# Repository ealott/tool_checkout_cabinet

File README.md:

# Wifi-Enabled RFID Cabinet Lock
An inexpensive, RFID-based door access solution for individual cabinets.  Based on Micropython and the ESP8266/ESP32 MCU.

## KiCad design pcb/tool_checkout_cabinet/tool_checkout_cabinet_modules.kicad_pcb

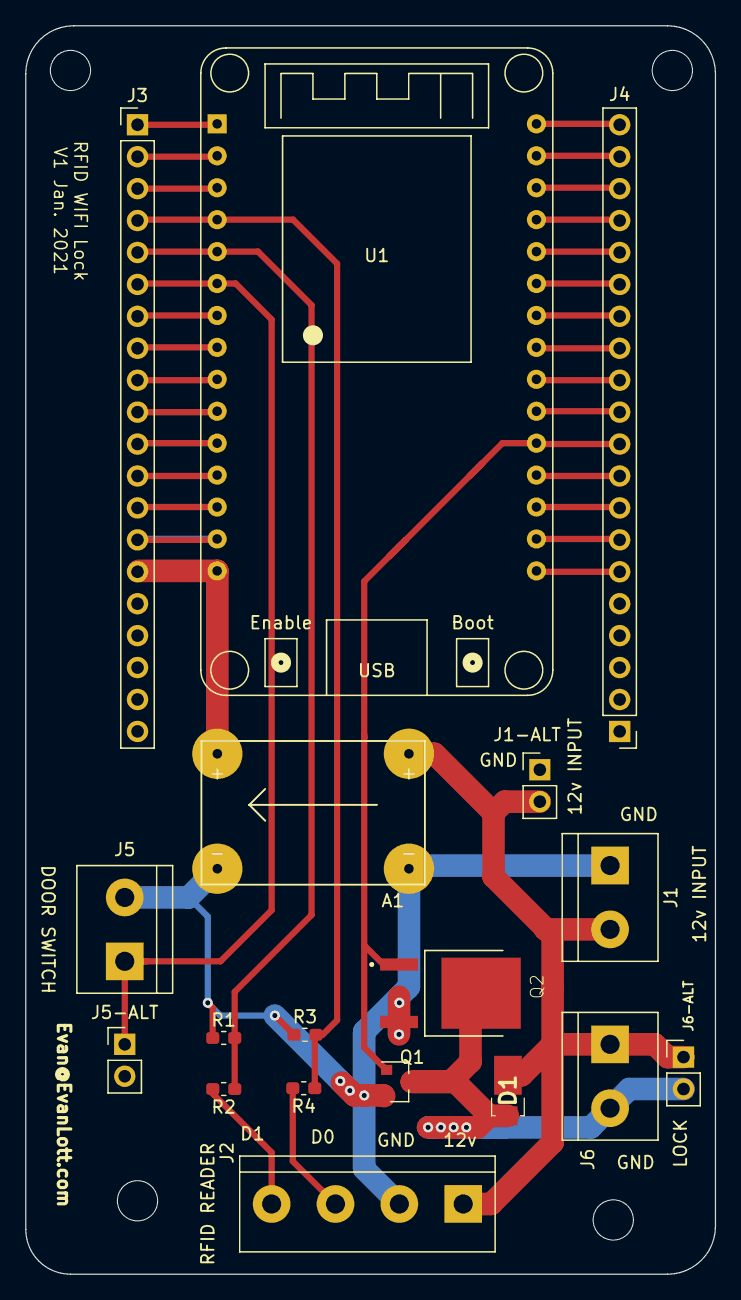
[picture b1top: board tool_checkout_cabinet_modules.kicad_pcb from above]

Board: 2 copper layers, 54.9 x 99.3 mm, 18 parts (0 on the bottom side), 33 nets.

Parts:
A1: Mini360_Module
D1: V8PAM10S-M3_H; V8PAM10SHM3H
J1, J5, J6: Screw_Terminal_01x02; TerminalBlock_bornier-2_P5.08mm
J1-ALT, J5-ALT, J6-ALT: PinHeader_1x02_P2.54mm_Vertical
J2: Screw_Terminal_01x04; TerminalBlock_bornier-4_P5.08mm
J3, J4: Conn_01x20_Male; PinHeader_1x20_P2.54mm_Vertical
Q1: DMG2302U; SOT-23
Q2: AOD4184A; DPAK228P994X240-4N
R1, R3: 10k; R_0603_1608Metric_Pad1.05x0.95mm_HandSolder
R2, R4: 4k7; R_0603_1608Metric_Pad1.05x0.95mm_HandSolder
U1: ESP32_DevKit_V1_DOIT; esp32_devkit_v1_doit

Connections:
+5V: A1.3, J3.15, U1.15
GND: A1.2, A1.4, J1.1, J1-ALT.1, J2.2, J3.14, J4.7, J5.2, J5-ALT.2, Q1.2, Q2.3, R1.1, R3.1, U1.14, U1.17
IO4: J4.10, Q1.1, Q2.1, U1.20
IO32: J3.6, J5.1, J5-ALT.1, U1.6
IO34: J3.4, R3.2, R4.1, U1.4
IO35: J3.5, R1.2, R2.1, U1.5
J6-12v: A1.1, D1.1, J1.2, J1-ALT.2, J2.1, J6.1, J6-ALT.1
unnamed: D1.2, J6.2, J6-ALT.2, Q1.3, Q2.4
unnamed: J2.3, R4.2
unnamed: J2.4, R2.2
unnamed: J3.1, U1.1
unnamed: J3.2, U1.2
unnamed: J3.3, U1.3
unnamed: J3.7, U1.7
unnamed: J3.8, U1.8
unnamed: J3.9, U1.9
unnamed: J3.10, U1.10
unnamed: J3.11, U1.11
unnamed: J3.12, U1.12
unnamed: J3.13, U1.13
unnamed: J4.6, U1.16
unnamed: J4.8, U1.18
unnamed: J4.9, U1.19
unnamed: J4.11, U1.21
unnamed: J4.12, U1.22
unnamed: J4.13, U1.23
unnamed: J4.14, U1.24
unnamed: J4.15, U1.25
unnamed: J4.16, U1.26
unnamed: J4.17, U1.27
unnamed: J4.18, U1.28
unnamed: J4.19, U1.29
unnamed: J4.20, U1.30

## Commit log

2020-08-30 initial commit of working system
2020-08-30 added bad read detection
2020-11-02 add some TODOs
2020-11-13 initial commit of PCB design
2020-11-13 renamed block diagram png
2020-11-13 Update README.md
    add esp32 to description
2021-01-28 v1 update
2021-01-28 Add 3D render image of PCB
2021-04-13 initial commit of AD caching system
2021-04-13 reorganize w/ docs directory; update KiCad project
2021-04-16 improve filename
2021-04-16 prune requirements
2021-04-16 initial commit of SystemD service file, makefile, env
2021-04-16 store some settings in ENV variables, add dotenv
2021-04-21 add dockerfile
2021-04-21 update entrypoint
2021-04-23 wait for network-online before starting service
2021-04-23 install python3-ldap package through system repos
2021-04-25 Fix broken image reference.
2021-05-31 Initital commit of working firmware
2021-07-30 Update to use caching, and properly convert raw RFID output to 10D format
2021-07-30 added output for 40bit IDs; removed unused arg; changed lock open time from 5 to 2 sec
2021-08-04 fixed bit mask
2022-03-21 Bump waitress from 2.0.0 to 2.1.1 in /ad_cache
    Bumps [waitress](https://github.com/Pylons/waitress) from 2.0.0 to 2.1.1.
    - [Release notes](https://github.com/Pylons/waitress/releases)
    - [Changelog](https://github.com/Pylons/waitress/blob/master/CHANGES.txt)
    - [Commits](https://github.com/Pylons/waitress/compare/v2.0.0...v2.1.1)
    ---
    updated-dependencies:
2023-02-16 Bump werkzeug from 1.0.1 to 2.2.3 in /ad_cache
    Bumps [werkzeug](https://github.com/pallets/werkzeug) from 1.0.1 to 2.2.3.
    - [Release notes](https://github.com/pallets/werkzeug/releases)
    - [Changelog](https://github.com/pallets/werkzeug/blob/main/CHANGES.rst)
    - [Commits](https://github.com/pallets/werkzeug/compare/1.0.1...2.2.3)
    ---
    updated-dependencies:
2023-05-01 Bump flask from 1.1.2 to 2.3.2 in /ad_cache
    Bumps [flask](https://github.com/pallets/flask) from 1.1.2 to 2.3.2.
    - [Release notes](https://github.com/pallets/flask/releases)
    - [Changelog](https://github.com/pallets/flask/blob/main/CHANGES.rst)
    - [Commits](https://github.com/pallets/flask/compare/1.1.2...2.3.2)
    ---
    updated-dependencies:
